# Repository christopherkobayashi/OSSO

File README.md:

# Osso

Osso is a BeagleBone (White/Black/Green) I/O expansion cape.

The Osso was designed by Franco (nextime) Lanza <franco@nexlab.it>

## Output

The Osso has 8 relays rated at 275VAC@10A.

## Input
Osso has 8 digital inputs.  They can be switched between opto-isolated and non-opto-isolated; the instructions are [here](INPUTS.md)

## Power

The expansion cape is powered by a 12VDC connector (9 to 24VDC supported).  The Osso will supply power to the BeagleBone via the expansion pins.

## Software

A test Debian GNU/Linux install is available.  Installation instructions are [here](TEST.md)

## Miscellaneous

The size of the cape is a standard format for 9 units DIN mount boxes.

## Pictures

Pin diagram (green dot pins are optional, other required):

## Miscellaneous

For more information, please visit https://www.nexlab.net/

Do you like our cape? Donations in Bitcoin is accepted at 1ABepVhyYuZNxiMQe8atPi4tRJZKkpRDqb (CK note: verify this address with nextime before sending any Bitcoin!)

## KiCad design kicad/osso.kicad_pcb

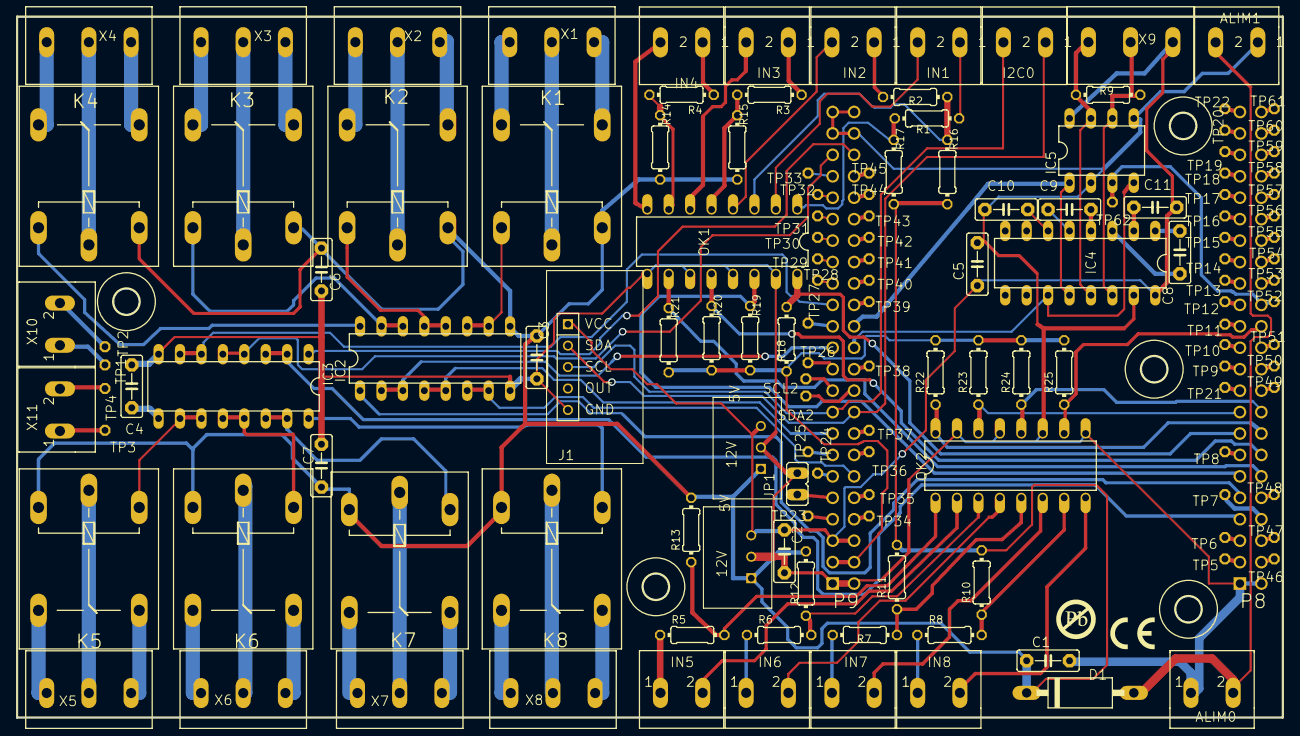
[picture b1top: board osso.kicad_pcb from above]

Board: 4 copper layers, 150.0 x 83.1 mm, 150 parts (1 on the bottom side), 154 nets.

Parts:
ALIM0, ALIM1: Alim; W237-102
C1, C2, C3, C4, C5, C6, C7, C8, C9, C10, C11: C5B2.5
D1: DIODE; DO15-12
H1, H2, H3, H4, H5: HOLE3.0; 3,0
I2C0: I2C; W237-102
IC1, IC6: REGOLATORE_TENSIONESWITCHING; MT6-3
IC2, IC3: ULN2003AN; DIL16
IC4: MAX202CPE; DIL16
IC5: MAX481CPA; DIL08
IN1: IN1; W237-102
IN2: IN2; W237-102
IN3: IN3; W237-102
IN4: IN4; W237-102
IN5: IN5; W237-102
IN6: IN6; W237-102
IN7: IN7; W237-102
IN8: IN8; W237-102
J1: RTC_MICROROBOT_ALGOZINO-PTH; RTC_MICROBOT_ALGOZINO
JP1: JP1
K1, K2, K3, K4, K5, K6, K7, K8: RELAY; G5LE
OK1, OK2: OPTOISOLATORE_ILQ620; DIL16
PCB1: BORDO_UNIXMEDIA150X83,5; BORD_UNIXMEDIA
R1, R2, R3, R4, R5, R6, R7, R8: 49; 0204_7
R9, R13, R15, R23: 0204_7
R10, R11, R12, R14, R16, R17, R18, R19, R20, R21, R22, R24, R25: 10k; 0204_7
SCL2: TPPAD1-13; TEST_POINT
SDA2: TP1; TEST_POINT
SS1: CE-MARK; CE-MARK-0.2
SS2: PB-MARK; PB-MARK-0.2
TP1, TP2, TP3, TP4, TP5, TP6, TP7, TP8, TP9, TP10, TP11, TP12, TP13, TP14, TP15, TP16, TP17, TP18, TP19, TP20, TP21, TP22, TP23, TP24, TP25, TP26, TP27, TP28, TP29, TP30, TP31, TP32, TP33, TP34, TP35, TP36, TP37, TP38, TP39, TP40, TP41, TP42, TP43, TP44, TP45, TP46, TP47, TP48, TP49, TP50, TP51, TP52, TP53, TP54, TP55, TP56, TP57, TP58, TP59, TP60, TP61, TP62: TPPAD1-13; TEST_POINT
U$1: BEAGLEBONE_OUTLINE; BEAGLEBONE_SHIELD
X1: X1; W237-103
X2: X2; W237-103
X3: X3; W237-103
X4: X4; W237-103
X5: X5; W237-103
X6: X6; W237-103
X7: X7; W237-103
X8: X8; W237-103
X9: W237-103
X10, X11: W237-102

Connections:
3.3V: R18.2, R19.2, R20.2, R21.2, R22.2, R23.2, R24.2, R25.2, U$1.49, U$1.50
5V: C2.1, C5.1, C11.1, IC1.3, IC4.16, IC5.8, IC6.3, J1.1, U$1.51, U$1.52, X9.1
12V: C1.1, C3.1, C6.1, C7.1, D1.C, IC1.1, IC2.9, IC6.1, K1.1, K2.1, K3.1, K4.1, K5.1, K6.1, K7.1, K8.1, R10.2, R11.2, R12.2, R13.2, R14.2, R15.2, R16.2, R17.2
ALIM: ALIM0.2, ALIM1.2, D1.A
BB_RX: IC4.12, IC5.1, U$1.72
BB_TX: IC4.11, IC5.4, U$1.70
BOB1: IC2.10, IC2.11, K1.2
BOB2: IC2.12, IC2.13, K2.2
BOB3: IC2.14, IC2.15, K3.2
BOB4: IC2.16, K4.2
BOB5: IC3.10, IC3.11, K5.2
BOB6: IC3.12, IC3.13, K6.2
BOB7: IC3.14, IC3.15, K7.2
BOB8: IC3.16, K8.2
GND: ALIM0.1, ALIM1.1, C1.2, C2.2, C3.2, C4.2, C5.2, C6.2, C7.2, C10.2, IC1.2, IC2.8, IC3.8, IC4.15, IC5.2, IC5.5, IC6.2, J1.5, JP1.1, OK1.9, OK1.11, OK1.13, OK1.15, OK2.9, OK2.11, OK2.13, OK2.15, U$1.1, U$1.2, U$1.47, U$1.48, U$1.89, U$1.90, U$1.91, U$1.92
I2C1_SCL: I2C0.2, J1.3, U$1.63
I2C1_SDA: I2C0.1, J1.2, U$1.64
I2C2_SCL: SCL2.TP, U$1.65
I2C2_SDA: SDA2.TP, U$1.66
IN1: OK1.16, R18.1, U$1.15
IN1_12V: OK1.1, R1.2, R17.1
IN2: OK1.14, R19.1, U$1.11
IN2_12V: OK1.3, R2.2, R16.1
IN3: OK1.12, R20.1, U$1.14
IN3_12V: OK1.5, R3.2, R15.1
IN4: OK1.10, R21.1, U$1.12
IN4_12V: OK1.7, R4.2, R14.1
IN5: OK2.16, R22.1, U$1.16
IN5_12V: OK2.1, R5.2, R13.1
IN6: OK2.14, R23.1, U$1.17
IN6_12V: OK2.3, R6.2, R12.1
IN7: OK2.12, R24.1, U$1.18
IN7_12V: OK2.5, R7.2, R11.1
IN8: OK2.10, R25.1, U$1.26
IN8_12V: OK2.7, R8.2, R10.1
unnamed: IN1.1, R1.1
unnamed: TP1.TP, X10.1
unnamed: K5.S, X5.1
unnamed: K5.P, X5.2
unnamed: K5.O, X5.3
unnamed: K6.S, X6.1
unnamed: K6.P, X6.2
unnamed: K6.O, X6.3
unnamed: K3.S, X3.1
unnamed: K3.P, X3.2
unnamed: K3.O, X3.3
unnamed: C4.1, IC3.9
unnamed: K7.S, X7.1
unnamed: K7.P, X7.2
unnamed: K4.S, X4.1
unnamed: K4.P, X4.2
unnamed: K4.O, X4.3
unnamed: K8.S, X8.1
unnamed: K8.P, X8.2
unnamed: K8.O, X8.3
unnamed: IN2.1, R2.1
unnamed: TP2.TP, X10.2
unnamed: IN3.1, R3.1
unnamed: TP3.TP, X11.1
unnamed: IN4.1, R4.1
unnamed: TP4.TP, X11.2
unnamed: IN5.1, R5.1
unnamed: TP7.TP, U$1.8
unnamed: IN6.1, R6.1
unnamed: TP22.TP, U$1.45
unnamed: IN7.1, R7.1
unnamed: TP20.TP, U$1.43
unnamed: IN8.1, R8.1
unnamed: TP19.TP, U$1.41
unnamed: IN8.2, OK2.8
unnamed: IN7.2, OK2.6
unnamed: IN6.2, OK2.4
unnamed: IN5.2, OK2.2
unnamed: IN1.2, OK1.2
unnamed: IN2.2, OK1.4
unnamed: IN3.2, OK1.6
unnamed: IN4.2, OK1.8
unnamed: JP1.2, U$1.55
unnamed: TP18.TP, U$1.39
unnamed: TP17.TP, U$1.37
unnamed: TP16.TP, U$1.35
unnamed: TP15.TP, U$1.33
unnamed: TP14.TP, U$1.31
unnamed: TP13.TP, U$1.29
unnamed: TP12.TP, U$1.27
unnamed: TP11.TP, U$1.25
unnamed: TP10.TP, U$1.23
unnamed: TP9.TP, U$1.21
unnamed: TP21.TP, U$1.19
unnamed: TP5.TP, U$1.3
unnamed: TP6.TP, U$1.5
unnamed: K7.O, X7.3
unnamed: TP8.TP, U$1.13
unnamed: TP33.TP, U$1.85
unnamed: TP32.TP, U$1.83
unnamed: TP31.TP, U$1.81
unnamed: TP30.TP, U$1.79
unnamed: TP29.TP, U$1.77
unnamed: TP28.TP, U$1.75
unnamed: TP27.TP, U$1.71
unnamed: TP26.TP, U$1.67
unnamed: TP25.TP, U$1.59
unnamed: TP24.TP, U$1.57
unnamed: TP23.TP, U$1.53
unnamed: TP34.TP, U$1.54
unnamed: TP35.TP, U$1.56
unnamed: TP36.TP, U$1.60
unnamed: TP37.TP, U$1.62
unnamed: TP38.TP, U$1.68
unnamed: TP39.TP, U$1.74
unnamed: TP40.TP, U$1.76
unnamed: TP41.TP, U$1.78
unnamed: TP42.TP, U$1.80
unnamed: TP43.TP, U$1.82
unnamed: TP44.TP, U$1.84
unnamed: TP45.TP, U$1.86
unnamed: TP61.TP, U$1.46
unnamed: TP60.TP, U$1.44
unnamed: TP59.TP, U$1.42
unnamed: TP58.TP, U$1.40
unnamed: TP57.TP, U$1.38
unnamed: TP56.TP, U$1.36
unnamed: TP55.TP, U$1.34
unnamed: TP54.TP, U$1.32
unnamed: TP53.TP, U$1.30
unnamed: TP51.TP, U$1.24
unnamed: TP50.TP, U$1.22
unnamed: TP49.TP, U$1.20
unnamed: TP48.TP, U$1.10
unnamed: TP47.TP, U$1.6
unnamed: TP46.TP, U$1.4
unnamed: C8.1, IC4.1
unnamed: C8.2, IC4.3
unnamed: C9.1, IC4.4
unnamed: C9.2, IC4.5
R1_C: K1.P, X1.2
R1_NA: K1.S, X1.1
R1_NC: K1.O, X1.3
R2_C: K2.P, X2.2
R2_NA: K2.S, X2.1
R2_NC: K2.O, X2.3
REL1: IC2.6, IC2.7, U$1.58
REL2: IC2.4, IC2.5, U$1.61
REL3: IC2.2, IC2.3, U$1.69
REL4: IC2.1, U$1.9
REL5: IC3.6, IC3.7, U$1.73
REL6: IC3.4, IC3.5, U$1.87
REL7: IC3.2, IC3.3, U$1.7
REL8: IC3.1, U$1.88
RS485_ENABLE: IC5.3, TP52.TP, TP62.TP, U$1.28
RX_B: IC4.13, IC5.7, R9.2, X9.3
TX_A: IC4.14, IC5.6, R9.1, X9.2
V+: C11.2, IC4.2
V-: C10.1, IC4.6

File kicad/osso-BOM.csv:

"Source:","/home/wileyc/src/OSSO/kicad/osso.kicad_sch"
"Date:","Fri 27 Jan 2023 08:09:53 PM JST"
"Tool:","Eeschema (6.0.11)"
"Generator:","/usr/share/kicad/plugins/bom_csv_grouped_by_value_with_fp.py"
"Component Count:","150"
"Ref","Qnty","Value","Cmp name","Footprint","Description","Vendor"
"ALIM0, ALIM1, ","2","Alim","MORSETTO_2","osso:W237-102","",""
"C1, C2, C3, C4, C5, C6, C7, C8, C9, C10, C11, ","11","C5/2.5","C5{slash}2.5","osso:C5B2.5","",""
"D1, ","1","DIODE","DIODE","osso:DO15-12","",""
"H1, H2, H3, H4, H5, ","5","HOLE3.0","HOLE3.0","osso:3,0","",""
"I2C0, ","1","I2C","MORSETTO_2","osso:W237-102","",""
"IC1, IC6, ","2","REGOLATORE_TENSIONESWITCHING","REGOLATORE_TENSIONESWITCHING","osso:MT6-3","",""
"IC2, IC3, ","2","ULN2003AN","ULN2003AN","osso:DIL16","",""
"IC4, ","1","MAX202CPE","MAX202CPE","osso:DIL16","",""
"IC5, ","1","MAX481CPA","MAX481CPA","osso:DIL08","",""
"IN1, ","1","IN1","MORSETTO_2","osso:W237-102","",""
"IN2, ","1","IN2","MORSETTO_2","osso:W237-102","",""
"IN3, ","1","IN3","MORSETTO_2","osso:W237-102","",""
"IN4, ","1","IN4","MORSETTO_2","osso:W237-102","",""
"IN5, ","1","IN5","MORSETTO_2","osso:W237-102","",""
"IN6, ","1","IN6","MORSETTO_2","osso:W237-102","",""
"IN7, ","1","IN7","MORSETTO_2","osso:W237-102","",""
"IN8, ","1","IN8","MORSETTO_2","osso:W237-102","",""
"J1, ","1","RTC_MICROROBOT_ALGOZINO-PTH","RTC_MICROROBOT_ALGOZINO-PTH","osso:RTC_MICROBOT_ALGOZINO","",""
"JP1, ","1","JUMPER_2","JUMPER_2","osso:JP1","",""
"K1, K2, K3, K4, K5, K6, K7, K8, ","8","RELAY","RELAY","osso:G5LE","",""
"OK1, OK2, ","2","OPTOISOLATORE_ILQ620","OPTOISOLATORE_ILQ620","osso:DIL16","",""
"PCB1, ","1","BORDO_UNIXMEDIA150X83,5","BORDO_UNIXMEDIA150X83,5","osso:BORD_UNIXMEDIA","",""
"R1, R2, R3, R4, R5, R6, R7, R8, ","8","49","RESISTOR0204{slash}7","osso:0204_7","",""
"R9, R13, R15, R23, ","4","RESISTOR0204/7","RESISTOR0204{slash}7","osso:0204_7","",""
"R10, R11, R12, R14, R16, R17, R18, R19, R20, R21, R22, R24, R25, ","13","10k","RESISTOR0204{slash}7","osso:0204_7","",""
"SCL2, ","1","TPPAD1-13","TPPAD1-13","osso:TEST_POINT","",""
"SDA2, ","1","TP1","TPPAD1-13","osso:TEST_POINT","",""
"SS1, ","1","CE-MARK","CE-MARK","osso:CE-MARK-0.2","",""
"SS2, ","1","PB-MARK","PB-MARK","osso:PB-MARK-0.2","",""
"TP1, TP2, TP3, TP4, TP5, TP6, TP7, TP8, TP9, TP10, TP11, TP12, TP13, TP14, TP15, TP16, TP17, TP18, TP19, TP20, TP21, TP22, TP23, TP24, TP25, TP26, TP27, TP28, TP29, TP30, TP31, TP32, TP33, TP34, TP35, TP36, TP37, TP38, TP39, TP40, TP41, TP42, TP43, TP44, TP45, TP46, TP47, TP48, TP49, TP50, TP51, TP52, TP53, TP54, TP55, TP56, TP57, TP58, TP59, TP60, TP61, TP62, ","62","TPPAD1-13","TPPAD1-13","osso:TEST_POINT","",""
"U$1, ","1","BEAGLEBONE_OUTLINE","BEAGLEBONE_OUTLINE","osso:BEAGLEBONE_SHIELD","",""
"X1, ","1","X1","MORSETTO_3","osso:W237-103","",""
"X2, ","1","X2","MORSETTO_3","osso:W237-103","",""
"X3, ","1","X3","MORSETTO_3","osso:W237-103","",""
"X4, ","1","X4","MORSETTO_3","osso:W237-103","",""
"X5, ","1","X5","MORSETTO_3","osso:W237-103","",""
"X6, ","1","X6","MORSETTO_3","osso:W237-103","",""
"X7, ","1","X7","MORSETTO_3","osso:W237-103","",""
"X8, ","1","X8","MORSETTO_3","osso:W237-103","",""
"X9, ","1","MORSETTO_3","MORSETTO_3","osso:W237-103","",""
"X10, X11, ","2","MORSETTO_2","MORSETTO_2","osso:W237-102","",""

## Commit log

2022-12-30 Initial import.
2022-12-30 Add KiCAD conversion.
2022-12-30 Move Eagle files to subdirectory.
2022-12-30 Remove zero-byte file.
2022-12-30 Move docs to doc/
2022-12-30 Add gerbers.
2023-01-27 Clean up docs a bit.
2023-01-27 Add test image instructions.
2023-01-27 Fix link.
2023-01-27 Add BOM and footprints.
2023-01-27 Rework documentation a bit more.
2023-01-27 *sigh* Whitespace.
2023-01-27 More typos.
2023-01-27 One more.
